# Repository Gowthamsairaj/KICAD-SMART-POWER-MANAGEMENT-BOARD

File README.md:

View this project on [CADLAB.io](https://cadlab.io/project/29900). 

# Smart Power Management Board  
Buck Converter + LDO Regulation + Input Protection

## 📌 Project Overview
This project is a compact and efficient power supply system designed to convert a higher DC input voltage into stable 5V and 3.3V outputs suitable for microcontrollers, sensors, and embedded platforms.

The board demonstrates practical power tree design, regulator selection, protection techniques, and PCB layout practices used in real products.

---

## 🎯 Features
- Wide DC input range (e.g., 12V–24V)
- Buck conversion to 5V
- Linear regulation to 3.3V
- Reverse polarity and surge protection
- Output filtering capacitors
- Test points for debugging
- Screw terminal I/O connectors
- Designed for manufacturability

---

## 🧠 System Architecture
DC Input → Protection → Buck (5V) → LDO (3.3V) → Load

---

## 🔧 Main Components
- LM2596 – Step-down buck regulator
- AMS1117-3.3 – Linear regulator
- Schottky diode – reverse protection
- TVS diode – surge suppression
- Inductor & capacitors – filtering
- Potentiometer – output adjust (if used)

---

## ⚡ Output Rails
| Rail | Purpose |
|------|--------|
| 5V   | Motors, relays, logic supply |
| 3.3V | MCU, sensors, communication modules |

---

## 🛡 Protection Implemented
- Input reverse polarity protection
- Over-voltage transient suppression
- Fuse / polyfuse ready design
- Bulk and decoupling capacitors

---

## 📐 PCB Design Highlights
- Separate power and signal routing
- Short high-current paths
- Proper grounding strategy
- Wide traces for power lines
- Industry standard footprints

---

## 🧪 Ideal Applications
- Embedded development boards
- IoT prototypes
- Industrial control units
- Robotics
- Automation projects

---

## 🚀 What This Project Demonstrates
- Understanding of DC-DC conversion
- Power integrity basics
- Thermal & current considerations
- Schematic to PCB workflow
- ERC / DRC clean design

---

## 🧰 Tools Used
- KiCad (Schematic & PCB)
- GitHub for version control

---

## 👤 Author
GOWTHAMA SAI RAJ R T

Electronics & Communication Engineering  
Interested in Embedded Systems & Hardware Design

---

## 📜 License
Open-source for learning and educational use.

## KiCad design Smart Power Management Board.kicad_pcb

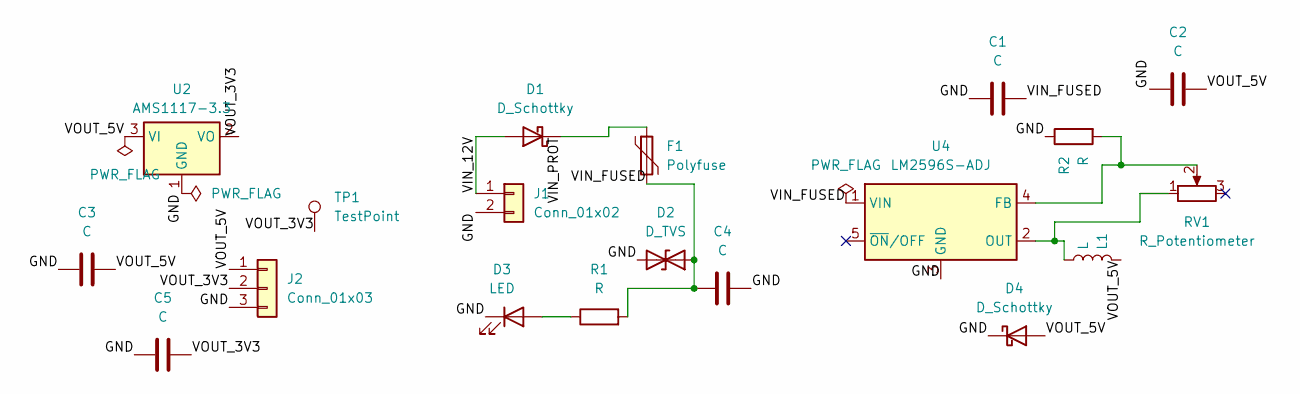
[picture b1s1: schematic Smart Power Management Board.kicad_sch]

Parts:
C1, C2: C; C_1206_3216Metric
C3, C5: C; C_0805_2012Metric
C4: C; CP_Radial_D8.0mm_P3.50mm
D1, D4: D_Schottky; D_SMA
D2: D_TVS; D_SMA
D3: LED; LED_0805_2012Metric
F1: Polyfuse; Fuse_1206_3216Metric
J1: Conn_01x02; PhoenixContact_MCV_1,5_2-G-5.08_1x02_P5.08mm_Vertical
J2: Conn_01x03; FanPinHeader_1x03_P2.54mm_Vertical
L1: L; L_Axial_L5.0mm_D3.6mm_P10.00mm_Horizontal_Murata_BL01RN1A2A2
R1, R2: R; R_0805_2012Metric
RV1: R_Potentiometer; Potentiometer_Bourns_3296W_Vertical
TP1: TestPoint; TestPoint_Pad_D1.5mm
U2: AMS1117-3.3; SOT-223-3_TabPin2
U4: LM2596S-ADJ; TO-263-5_TabPin3

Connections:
/GND: C1.1, C2.1, C3.1, C4.2, C5.1, D2.2 (A2), D3.1 (K), D4.1 (K), J1.2, J2.3, R2.1, U2.1 (GND), U4.3 (GND)
/VIN_12V: D1.2 (A), J1.1
/VIN_FUSED: C1.2, C4.1, D2.1 (A1), F1.2, R1.2, U4.1 (VIN)
/VIN_PROT: D1.1 (K), F1.1
/VOUT_3V3: C5.2, J2.2, TP1.1, U2.2 (VO)
/VOUT_5V: C2.2, C3.2, D4.2 (A), J2.1, L1.1, U2.3 (VI)
unnamed: D3.2 (A), R1.1
unnamed: R2.2, RV1.2, U4.4 (FB)
unnamed: L1.2, RV1.1, U4.2 (OUT)

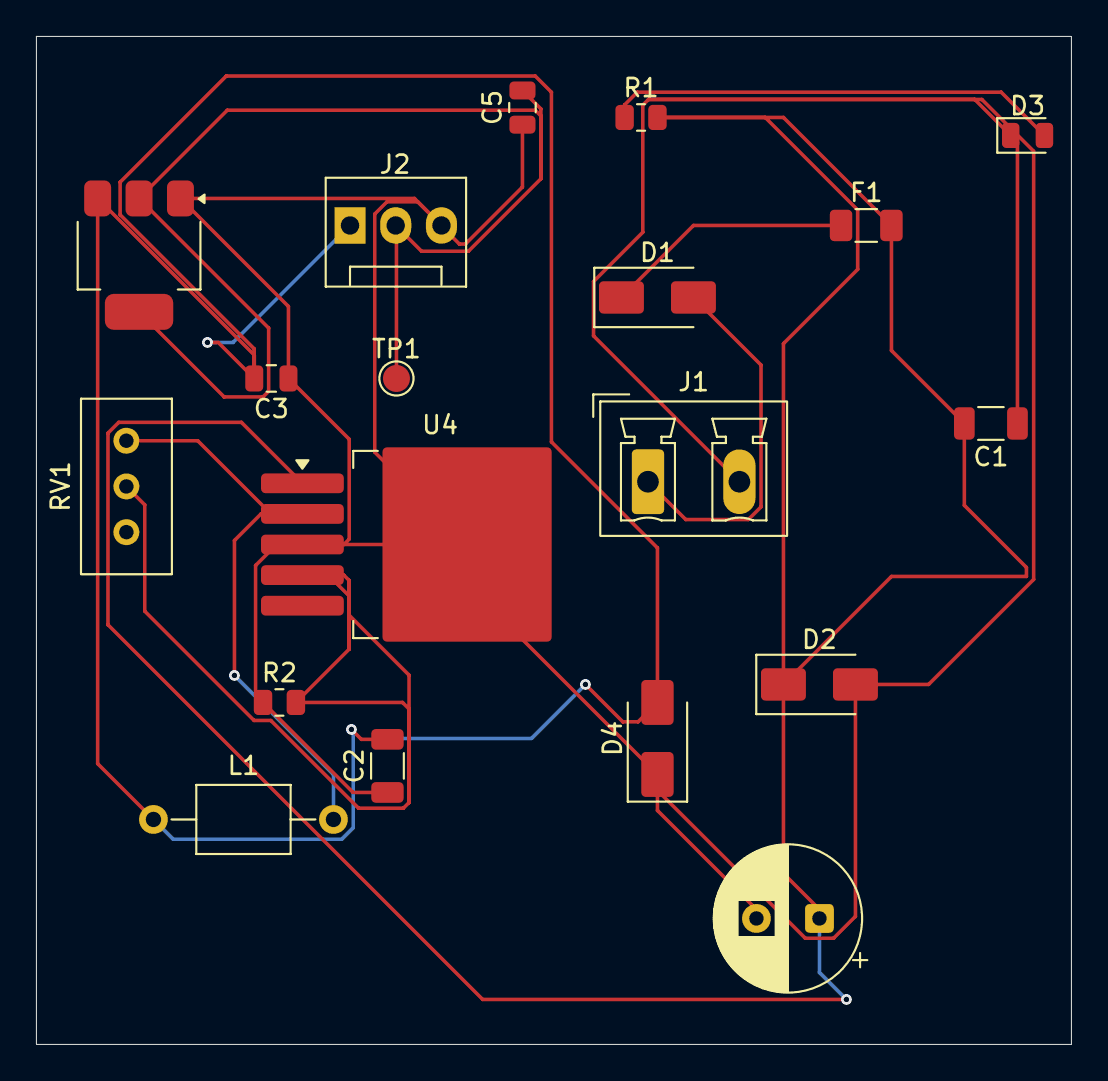
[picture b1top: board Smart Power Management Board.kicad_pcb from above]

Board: 2 copper layers, 57.5 x 56.0 mm, 19 parts (0 on the bottom side), 9 nets.

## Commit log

2026-02-07 SMART MULTI-POWER MANAGEMENT BOARD
2026-02-07 Backlink to CADLAB.io has been added.
2026-02-08 Revise README with project details and structure
    Updated project title and added detailed project overview, features, system architecture, main components, output rails, protection implemented, PCB design highlights, ideal applications, project dem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
